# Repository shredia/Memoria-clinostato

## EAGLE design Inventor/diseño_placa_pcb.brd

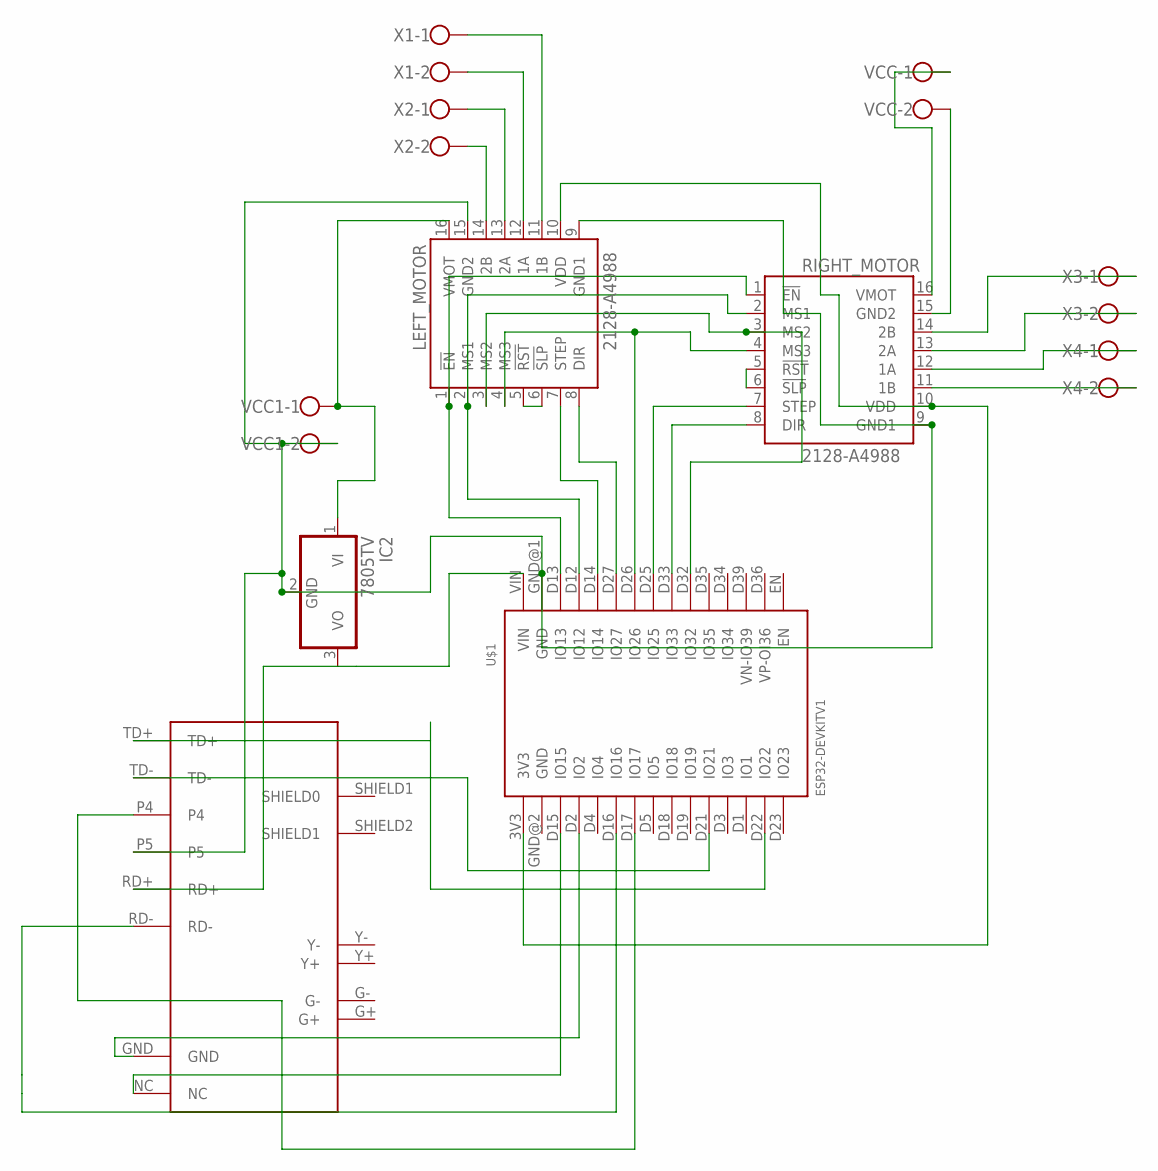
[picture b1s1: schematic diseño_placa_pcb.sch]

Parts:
IC2: 7805TV; TO220V
LEFT_MOTOR: 2128-A4988; A4988
RIGHT_MOTOR: 2128-A4988; A4988
U$1: ESP32DEVKITV1; ESP32-DEVKITV1
U$2: HR911105A; RJ45
VCC, VCC1: W237-102
X1, X2, X3, X4: W237-102

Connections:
unnamed: LEFT_MOTOR.1 (!EN), RIGHT_MOTOR.1 (!EN), U$1.D13 (IO13)
unnamed: LEFT_MOTOR.2 (MS1), RIGHT_MOTOR.2 (MS1), U$1.D12 (IO12)
unnamed: LEFT_MOTOR.3 (MS2), RIGHT_MOTOR.3 (MS2), U$1.D32 (IO32)
unnamed: RIGHT_MOTOR.12 (1A), X4.1
unnamed: LEFT_MOTOR.4 (MS3), RIGHT_MOTOR.4 (MS3), U$1.D26 (IO26)
unnamed: RIGHT_MOTOR.5 (!RST), RIGHT_MOTOR.6 (!SLP)
unnamed: LEFT_MOTOR.7 (STEP), U$1.D14 (IO14)
unnamed: LEFT_MOTOR.5 (!RST), LEFT_MOTOR.6 (!SLP)
unnamed: LEFT_MOTOR.8 (DIR), U$1.D27 (IO27)
unnamed: RIGHT_MOTOR.7 (STEP), U$1.D25 (IO25)
unnamed: RIGHT_MOTOR.8 (DIR), U$1.D33 (IO33)
unnamed: IC2.2 (GND), LEFT_MOTOR.9 (GND1), LEFT_MOTOR.15 (GND2), RIGHT_MOTOR.9 (GND1), U$1.GND@1 (GND), U$2.P5, VCC1.2
unnamed: IC2.3 (VO), U$1.VIN, U$2.RD+
unnamed: RIGHT_MOTOR.15 (GND2), VCC.2
unnamed: LEFT_MOTOR.10 (VDD), RIGHT_MOTOR.10 (VDD), U$1.3V3
unnamed: RIGHT_MOTOR.16 (VMOT), VCC.1
unnamed: RIGHT_MOTOR.14 (2B), X3.1
unnamed: RIGHT_MOTOR.13 (2A), X3.2
unnamed: LEFT_MOTOR.11 (1B), X1.1
unnamed: RIGHT_MOTOR.11 (1B), X4.2
unnamed: LEFT_MOTOR.12 (1A), X1.2
unnamed: LEFT_MOTOR.13 (2A), X2.1
unnamed: LEFT_MOTOR.14 (2B), X2.2
unnamed: U$1.D16 (IO16), U$2.RD-
unnamed: IC2.1 (VI), LEFT_MOTOR.16 (VMOT), VCC1.1
unnamed: U$1.D22 (IO22), U$2.TD+
unnamed: U$1.D21 (IO21), U$2.TD-
unnamed: U$1.D17 (IO17), U$2.P4
unnamed: U$1.D2 (IO2), U$2.GND
unnamed: U$1.D15 (IO15), U$2.NC

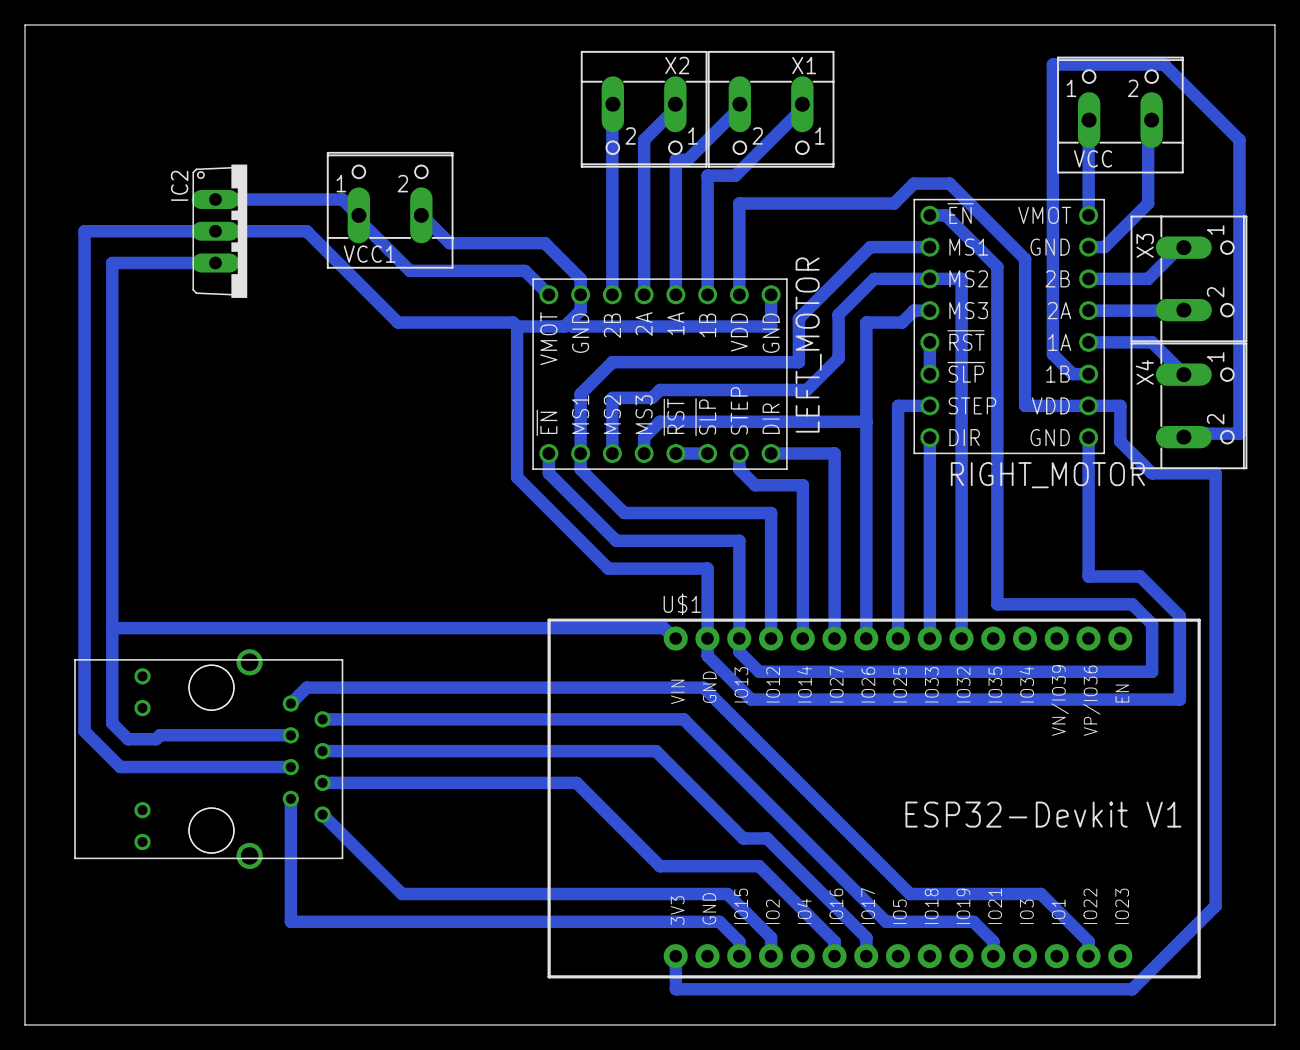
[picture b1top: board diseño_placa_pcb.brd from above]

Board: 2 copper layers, 100.0 x 80.0 mm, 11 parts (0 on the bottom side), 30 nets.

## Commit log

2025-05-16 primera subida
2025-05-19 se agregó un primer modelado del motor además de unos papers
2025-05-19 se subieron las iplementaciones de oficina
2025-05-27 se creó el código del SPWM del esp-idf
2025-05-27 se configuró el PLL para la transformada de park
2025-07-07 eagle design
2025-07-07 pcb_design
2025-07-08 otro diseño pcb
    diseño considerando 1.2 mm
2025-07-09 diseño pcb
    se realizó el diseño PCB considerando pistas de 1 mm
2025-07-30 codigo esp32 y caja pcb
2025-07-30 cmake esp32
    tiene problema que no encuentra el "AccelStepper.h"
2025-07-31 Creacion: Componentes LP8,motores y AccelStepper
2025-08-02 se crearon clases
2025-08-04 Create accelStepper
2025-08-04 Update AccelStepper
2025-08-14 Se modificaron las librerias de reconocimiento de información LP8
2025-08-14 Se creó la libreria wifi
    y puta que fué un dolor de cabeza
2025-08-18 Diferentes modificaciones: App_Mqt, control motores, Variables globales
2025-08-19 Se creó un documento word
2025-08-20 Creación de doble tasks a bajo ms
2025-08-20 Tasks motor in nucleo1 works
2025-08-20 definición de pines de salida, control de dirección habilitado
2025-08-20 Librerias LP8 y comprobación. Falta comprobar
2025-08-21 Se estabiliza la comunicación LP8
2025-08-25 nueva rama para salvar LP8
2025-08-25 se creó la carptea bme280
2025-08-25 ónLP8: Auto stash before merge of "resurrecciónLP8" and "Developer"
2025-08-25 Revert "ónLP8: Auto stash before merge of "resurrecciónLP8" and "Developer""
    This reverts commit 09935a00c613aaedba4bdea5304b57de603cbf36.
2025-08-25 Versión estable y salvada de LP8 y BME280
2025-08-25 se agregó el .gitignore
2025-08-27 Se subieron algunos pdf´s
2025-08-27 Fix: elimina mapeo de submódulo fantasma de AccelStepper
2025-08-27 Add: AccelStepper como carpeta normal (ya no submódulo)
2025-08-27 Fix: AccelStepper ahora como carpeta normal (sin repo embebido)
2025-08-27 untracked carpetas pc
2025-09-07 se hicieron muchos cambios
2025-09-08 cambio de carpeta de control robusto
2025-09-16 diseño bme y codigo mqtt
    se cambió el programa de grafico y control para conectarse al mqtt cambiado. Adicionalmente, se agregaron unos diseños del bme280
2025-09-16 main error?
2025-09-16 actualizacion aplicación
2025-09-22 cambios STL, ESP32 y app.py
    App.py: se modularizó la aplicación para un mejor trabajo, se creó una carpeta para cada sensor esp32 con subarchivos para cada txt, además de modificar la velocidad para mantener la relación de la f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
    ESP32: Se modificó el comando de calibrar que tenía mal el comando, generando error de medición.
    STL: se agregó el diseño que sostendrá los sensores
2025-09-25 Se modificó el programa de python como de la esp32.
    python: graficas mejoradas
    esp32: se agregó el feedback del LP8
2025-09-25 ahora si se subió bien el repo del commit anterior
2025-09-25 se agregó al txt la temperatura de los LP8
2025-09-29 papers
2025-09-29 Agrego carpeta Control Robusto
2025-10-03 no sé que pasa pero hago el commit igual
2025-10-03 diseños ycambios x
